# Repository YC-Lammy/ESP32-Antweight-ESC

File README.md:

# ESP32-Antweight-ESC
 A reciever and ESC capable of driving one brushless motor, two servos and two N20 motors. Designed for the UK antweight.

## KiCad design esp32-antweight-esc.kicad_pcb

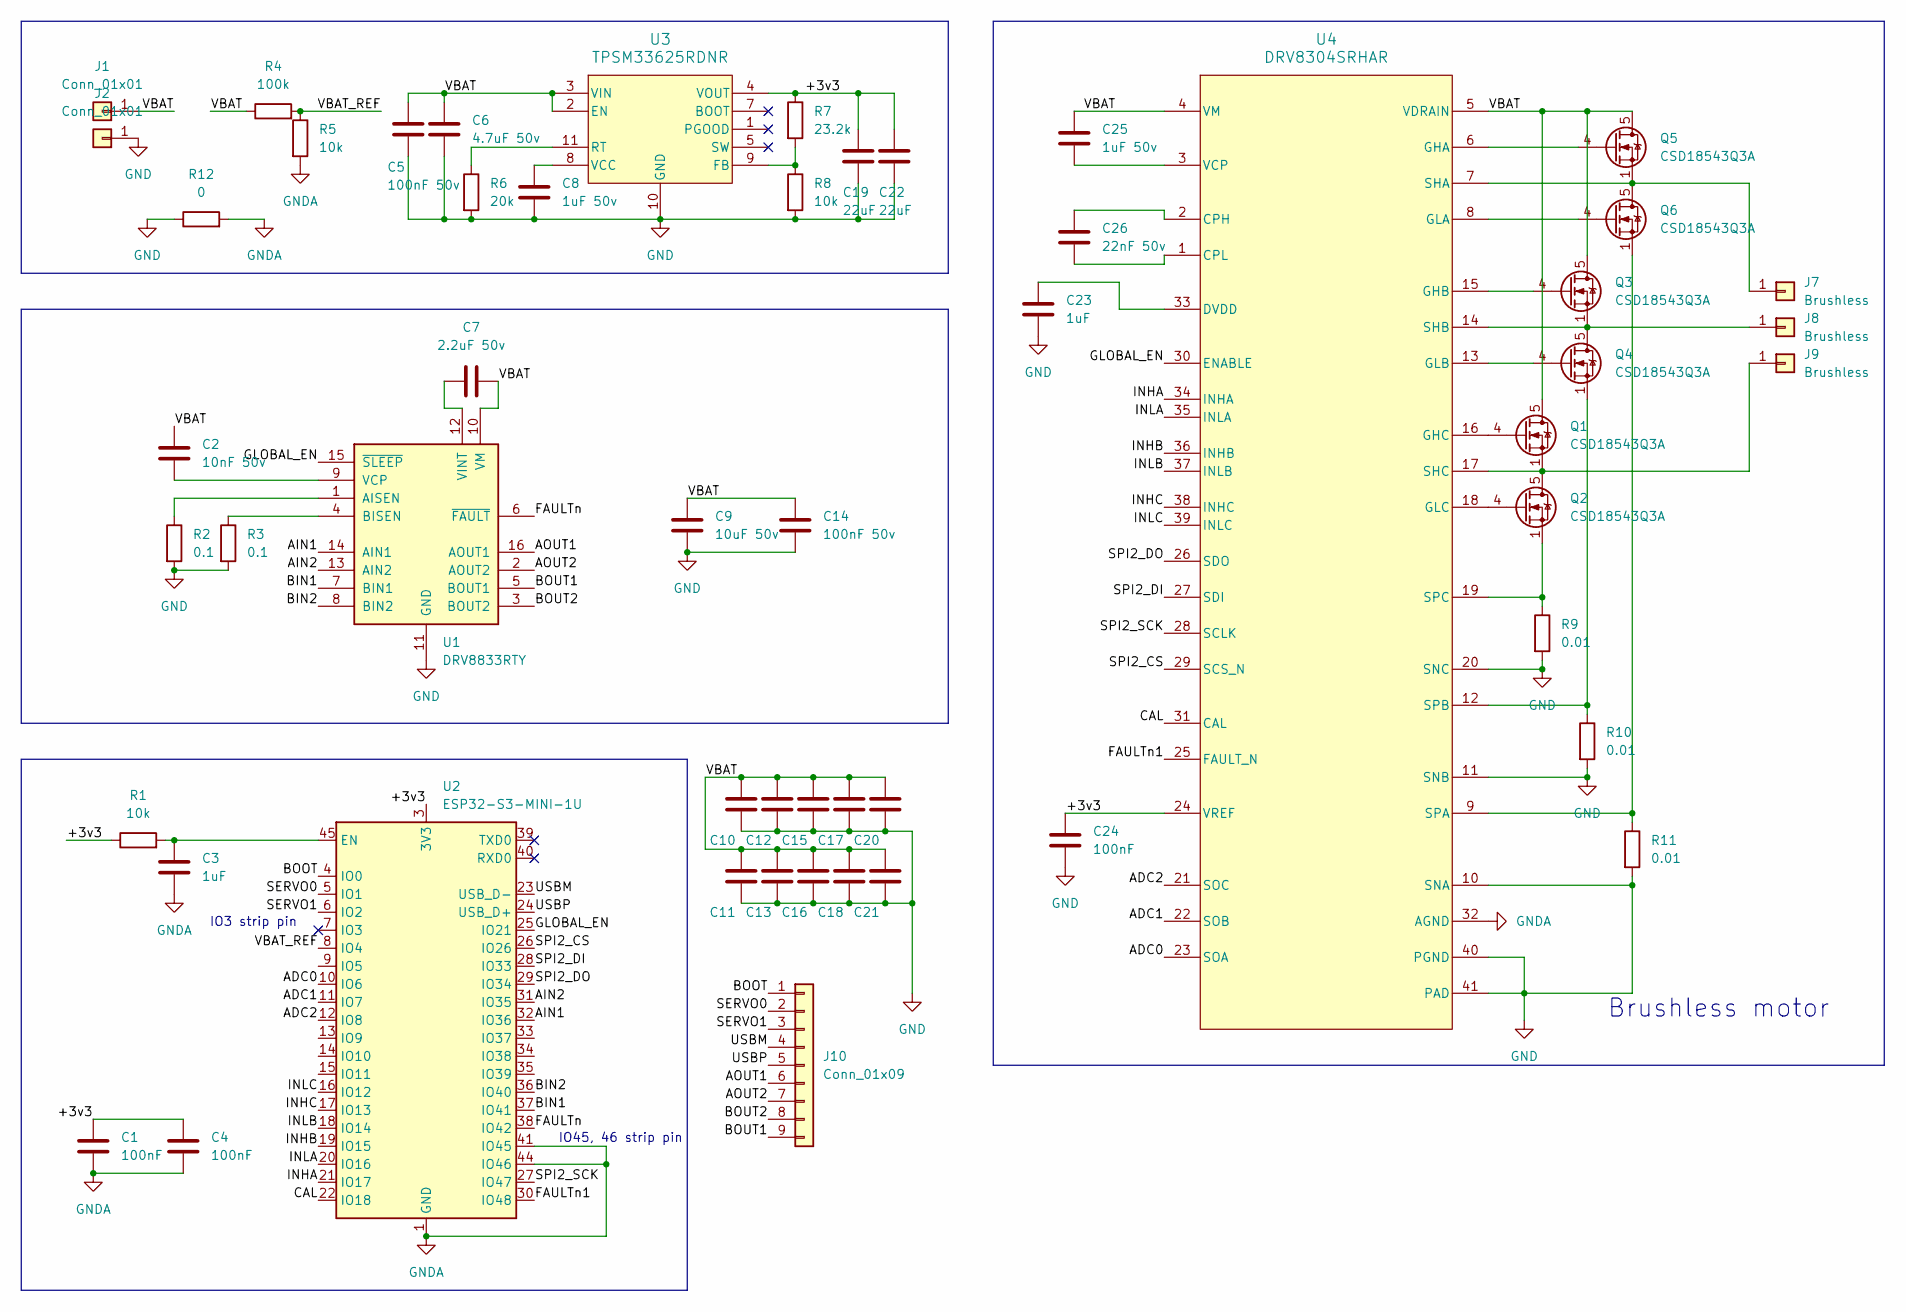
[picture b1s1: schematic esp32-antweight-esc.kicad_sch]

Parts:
C1, C4, C24: 100nF; C_0402_1005Metric
C2: 10nF 50v; C_0402_1005Metric
C3, C23: 1uF; C_0402_1005Metric
C5, C14: 100nF 50v; C_0402_1005Metric
C6: 4.7uF 50v; C_0805_2012Metric
C7: 2.2uF 50v; C_0603_1608Metric
C8, C25: 1uF 50v; C_0603_1608Metric
C9, C10, C11, C12, C13, C15, C16, C17, C18, C20, C21: 10uF 50v; C_0805_2012Metric
C19, C22: 22uF; C_0603_1608Metric
C26: 22nF 50v; C_0402_1005Metric
J1, J2: Conn_01x01; wire_pad_3.5mm
J7, J8, J9: Brushless; wire_pad_3.5mm
J10: Conn_01x09; wire_smd_1mm_9
Q1, Q2, Q3, Q4, Q5, Q6: CSD18543Q3A; VSON-8_3.3x3.3mm_P0.65mm_NexFET
R1, R5, R8: 10k; R_0402_1005Metric
R2, R3: 0.1; R_0402_1005Metric_Pad0.72x0.64mm_HandSolder
R4: 100k; R_0402_1005Metric
R6: 20k; R_0402_1005Metric
R7: 23.2k; R_0402_1005Metric
R9, R10, R11: 0.01; R_1206_3216Metric
R12: 0; R_0805_2012Metric
U1: DRV8833RTY; Texas_RTY_WQFN-16-1EP_4x4mm_P0.65mm_EP2.1x2.1mm_ThermalVias
U2: ESP32-S3-MINI-1U; ESP32-S2-MINI-1U
U3: TPSM33625RDNR; RDN0011A-MFG
U4: DRV8304SRHAR; Texas_RHA0040D_VQFN-40-1EP_6x6mm_P0.5mm_EP2.9x2.9mm_Thermal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

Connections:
/+3v3: C1.1, C4.1, C19.1, C22.1, C24.1, R1.1, R7.1, U2.3 (3V3), U3.4 (VOUT), U4.24 (VREF)
/ADC0: U2.10 (IO6), U4.23 (SOA)
/ADC1: U2.11 (IO7), U4.22 (SOB)
/ADC2: U2.12 (IO8), U4.21 (SOC)
/AIN1: U1.14 (AIN1), U2.32 (IO36)
/AIN2: U1.13 (AIN2), U2.31 (IO35)
/AOUT1: J10.6, U1.16 (AOUT1)
/AOUT2: J10.7, U1.2 (AOUT2)
/BIN1: U1.7 (BIN1), U2.37 (IO41)
/BIN2: U1.8 (BIN2), U2.36 (IO40)
/BOOT: J10.1, U2.4 (IO0)
/BOUT1: J10.9, U1.5 (BOUT1)
/BOUT2: J10.8, U1.3 (BOUT2)
/CAL: U2.22 (IO18), U4.31 (CAL)
/FAULTn: U1.6 (~FAULT), U2.38 (IO42)
/FAULTn1: U2.30 (IO48), U4.25 (FAULT_N)
/GLOBAL_EN: U1.15 (~SLEEP), U2.25 (IO21), U4.30 (ENABLE)
/INHA: U2.21 (IO17), U4.34 (INHA)
/INHB: U2.19 (IO15), U4.36 (INHB)
/INHC: U2.17 (IO13), U4.38 (INHC)
/INLA: U2.20 (IO16), U4.35 (INLA)
/INLB: U2.18 (IO14), U4.37 (INLB)
/INLC: U2.16 (IO12), U4.39 (INLC)
/SERVO0: J10.2, U2.5 (IO1)
/SERVO1: J10.3, U2.6 (IO2)
/SPI2_CS: U2.26 (IO26), U4.29 (SCS_N)
/SPI2_DI: U2.28 (IO33), U4.27 (SDI)
/SPI2_DO: U2.29 (IO34), U4.26 (SDO)
/SPI2_SCK: U2.27 (IO47), U4.28 (SCLK)
/USBM: J10.4, U2.23 (USB_D-)
/USBP: J10.5, U2.24 (USB_D+)
/VBAT: C2.1, C5.2, C6.1, C7.2, C9.1, C10.1, C11.1, C12.1, C13.1, C14.1, C15.1, C16.1, C17.1, C18.1, C20.1, C21.1, C25.1, J1.1, Q1.5 (D), Q3.5 (D), Q5.5 (D), R4.1, U1.10 (VM), U3.2 (EN), U3.3 (VIN), U4.4 (VM), U4.5 (VDRAIN)
/VBAT_REF: R4.2, R5.1, U2.8 (IO4)
GND: C5.1, C6.2, C8.2, C9.2, C10.2, C11.2, C12.2, C13.2, C14.2, C15.2, C16.2, C17.2, C18.2, C19.2, C20.2, C21.2, C22.2, C23.2, C24.2, J2.1, R2.2, R3.2, R6.2, R8.2, R9.2, R10.2, R11.2, R12.1, U1.11 (GND), U1.17 (GND), U3.10 (GND), U4.10 (SNA), U4.11 (SNB), U4.20 (SNC), U4.40 (PGND), U4.41 (PAD)
GNDA: C1.2, C3.2, C4.2, R5.2, R12.2, U2.1 (GND), U2.2 (GND), U2.41 (IO45), U2.42 (GND), U2.43 (GND), U2.44 (IO46), U2.46 (GND), U2.47 (GND), U2.48 (GND), U2.49 (GND), U2.50 (GND), U2.51 (GND), U2.52 (GND), U2.53 (GND), U2.54 (GND), U2.55 (GND), U2.56 (GND), U2.57 (GND), U2.58 (GND), U2.59 (GND), U2.60 (GND), U2.61 (GND), U2.62 (GND), U2.63 (GND), U2.64 (GND), U2.65 (GND), U4.32 (AGND)
unnamed: J7.1, Q5.1 (S), Q5.2 (S), Q5.3 (S), Q6.5 (D), U4.7 (SHA)
unnamed: J8.1, Q3.1 (S), Q3.2 (S), Q3.3 (S), Q4.5 (D), U4.14 (SHB)
unnamed: J9.1, Q1.1 (S), Q1.2 (S), Q1.3 (S), Q2.5 (D), U4.17 (SHC)
unnamed: Q1.4 (G), U4.16 (GHC)
unnamed: Q2.4 (G), U4.18 (GLC)
unnamed: Q3.4 (G), U4.15 (GHB)
unnamed: Q4.4 (G), U4.13 (GLB)
unnamed: Q5.4 (G), U4.6 (GHA)
unnamed: Q6.4 (G), U4.8 (GLA)
unnamed: R2.1, U1.1 (AISEN)
unnamed: R3.1, U1.4 (BISEN)
unnamed: C2.2, U1.9 (VCP)
unnamed: C7.1, U1.12 (VINT)
unnamed: C3.1, R1.2, U2.45 (EN)
unnamed: R7.2, R8.1, U3.9 (FB)
unnamed: R6.1, U3.11 (RT)
unnamed: C8.1, U3.8 (VCC)
unnamed: C26.1, U4.2 (CPH)
unnamed: C26.2, U4.1 (CPL)
unnamed: C23.1, U4.33 (DVDD)
unnamed: Q6.1 (S), Q6.2 (S), Q6.3 (S), R11.1, U4.9 (SPA)
unnamed: Q4.1 (S), Q4.2 (S), Q4.3 (S), R10.1, U4.12 (SPB)
unnamed: Q2.1 (S), Q2.2 (S), Q2.3 (S), R9.1, U4.19 (SPC)
unnamed: C25.2, U4.3 (VCP)

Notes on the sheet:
IO45, 46 strip pin
Brushless motor
IO3 strip pin

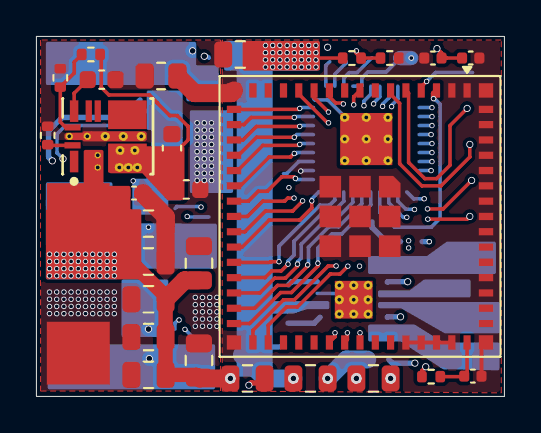
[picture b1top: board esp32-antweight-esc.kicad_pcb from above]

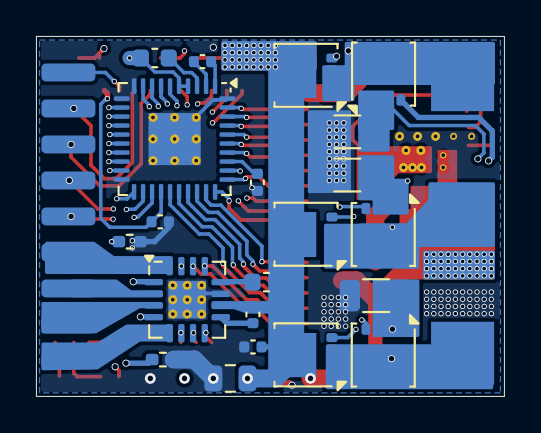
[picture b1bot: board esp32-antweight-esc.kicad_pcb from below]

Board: 4 copper layers, 26.0 x 20.0 mm, 54 parts (25 on the bottom side), 59 nets.

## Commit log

2025-02-20 main
